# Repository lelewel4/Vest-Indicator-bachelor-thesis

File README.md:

The engineering diploma thesis describes the design of a signal vest for an electric scooter driver based on wireless communication and STM32 microcontrollers.

The work contains a short introduction to the subject of e-scooters, after which the goal and scope of the project were defined. Existing commercial signal vest solutions were also reviewed. Then, the components enabling wireless communication were analyzed and development kits were selected. The entire project was divided into two parts: transmitting and receiving. Their appropriate functionality and requirements are outlined. Both parts discuss and justify the choice of specific electronic components. Electrical diagrams and printed circuits designed in KiCad are also presented. After this part, the PCBs were manufactured along with the assembly of elements. The subsections devoted to the software present the CubeMX environment, block diagrams, used libraries and interesting fragments of the source code written in C. Then, in the Tinkercad program, the appropriate housings were designed and manufactured in 3D technology. After assembling the project, functional tests were carried out.
The summary contains conclusions and further development directions for the project of a signaling vest for an electric scooter driver.

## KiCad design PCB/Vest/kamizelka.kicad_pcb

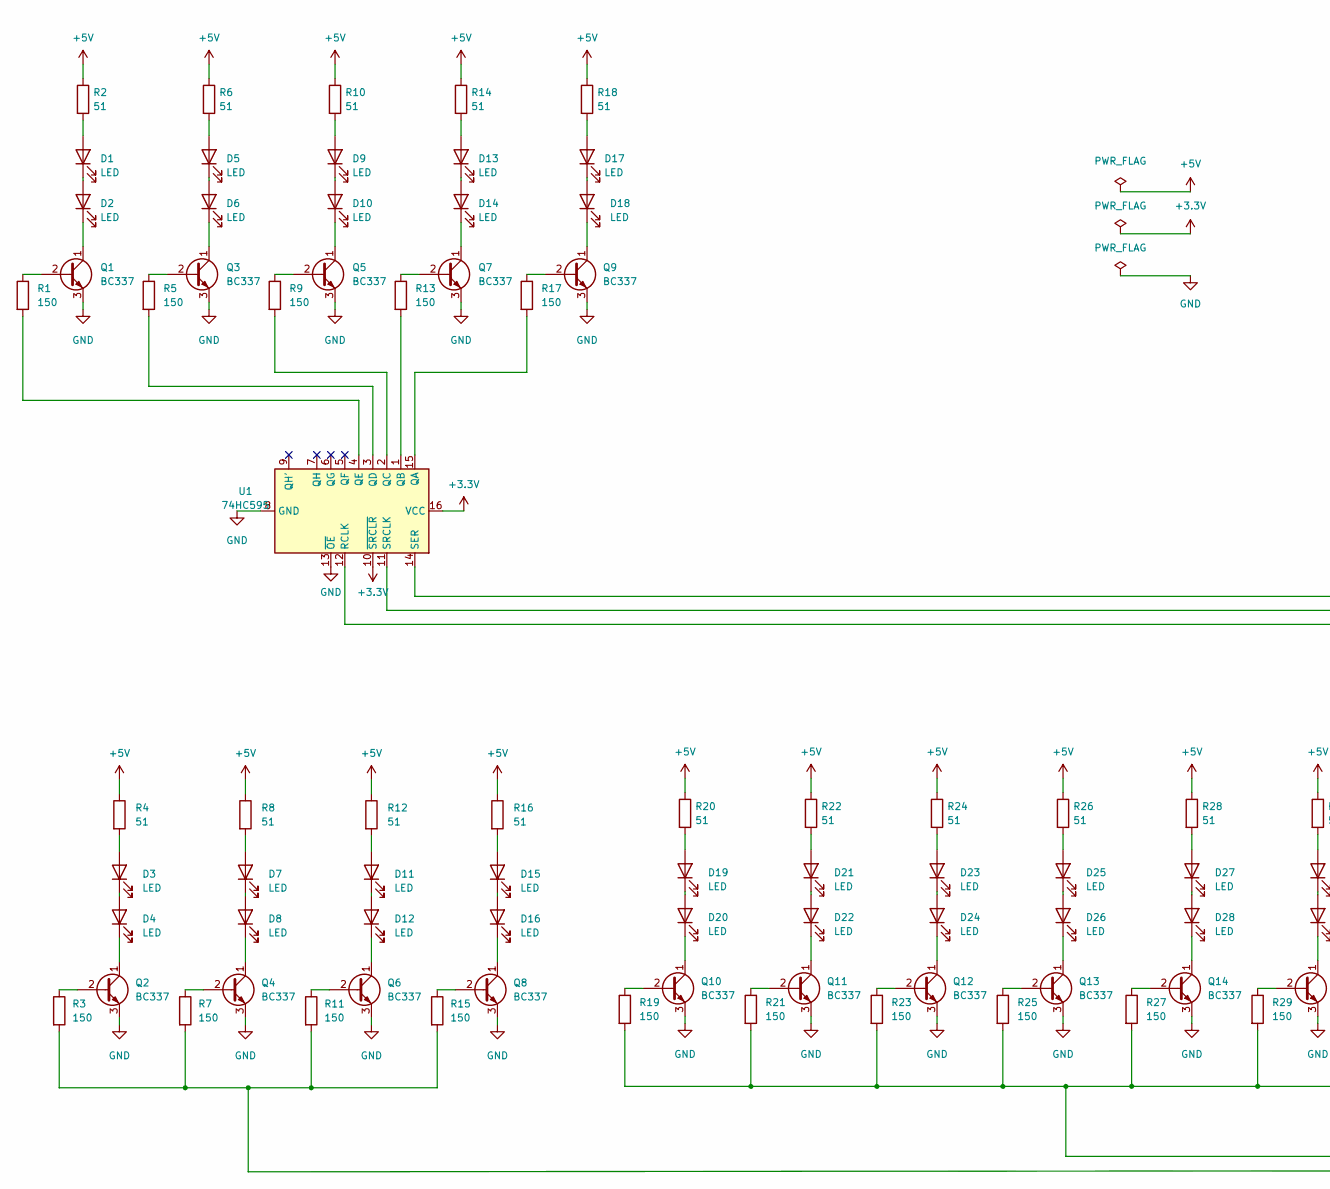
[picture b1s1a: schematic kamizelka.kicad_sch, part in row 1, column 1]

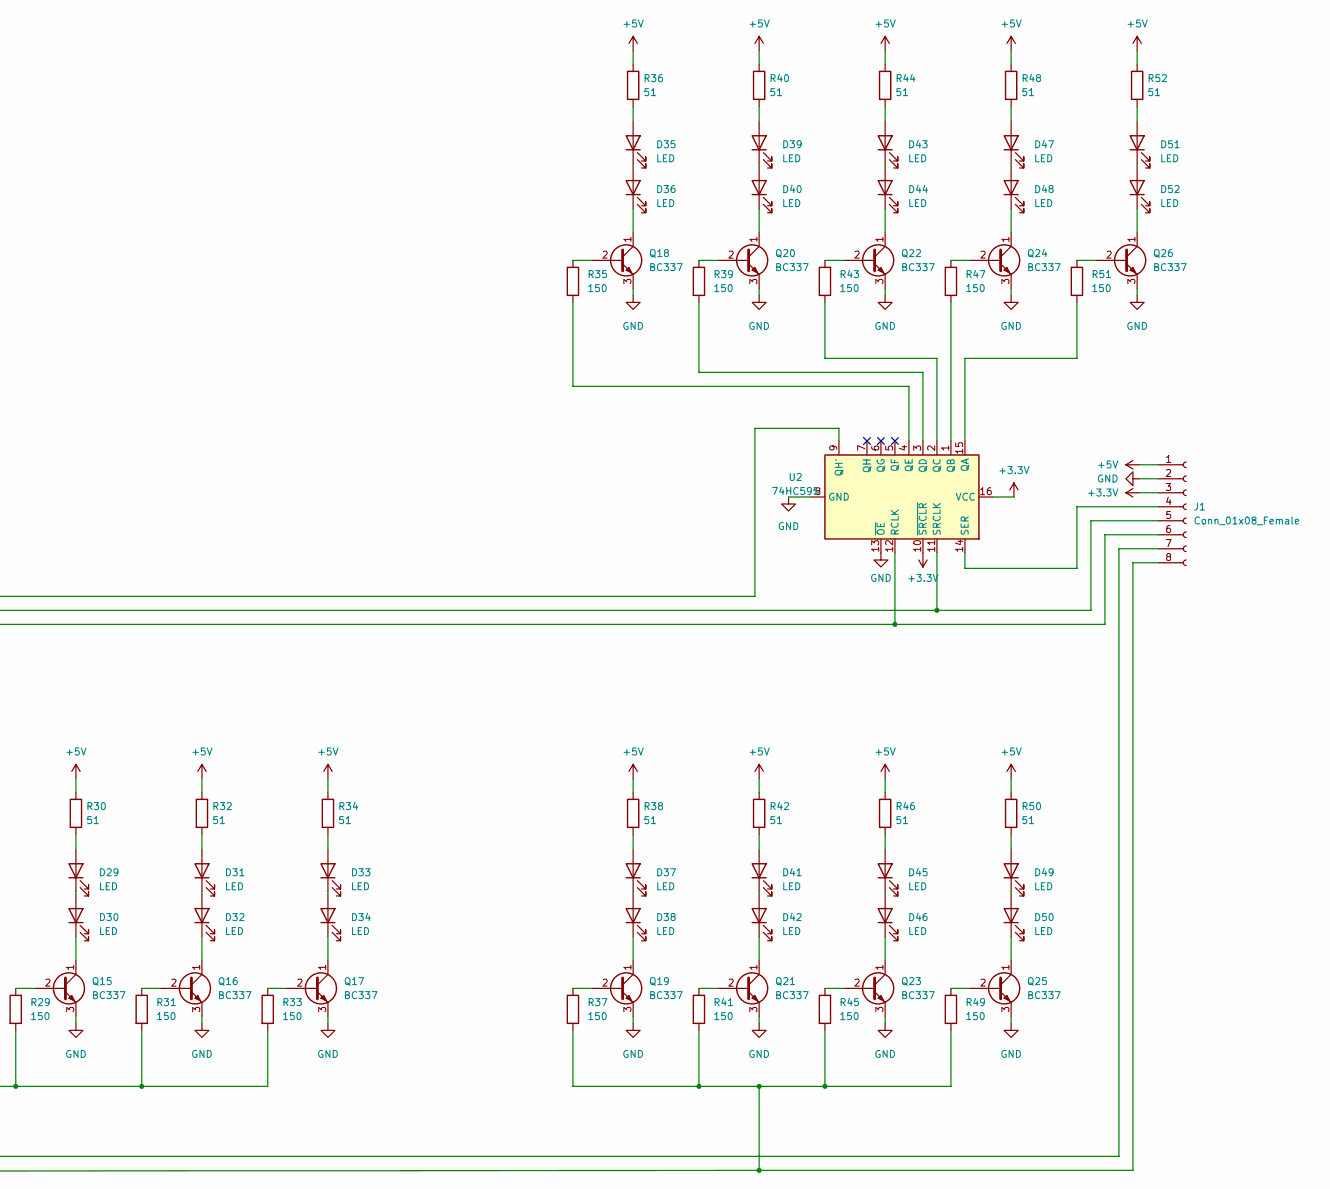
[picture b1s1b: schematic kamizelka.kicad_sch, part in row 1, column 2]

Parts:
D1, D2, D3, D4, D5, D6, D7, D8, D9, D10, D11, D12, D13, D14, D15, D16, D17, D18, D19, D20, D21, D22, D23, D24, D25, D26, D27, D28, D29, D30, D31, D32, D33, D34, D35, D36, D37, D38, D39, D40, D41, D42, D43, D44, D45, D46, D47, D48, D49, D50, D51, D52: LED; LED_D5.0mm
J1: Conn_01x08_Female; PinHeader_1x08_P2.54mm_Horizontal
Q1, Q2, Q3, Q4, Q5, Q6, Q7, Q8, Q9, Q10, Q11, Q12, Q13, Q14, Q15, Q16, Q17, Q18, Q19, Q20, Q21, Q22, Q23, Q24, Q25, Q26: BC337; TO-92_Inline
R1, R3, R5, R7, R9, R11, R13, R15, R17, R19, R21, R23, R25, R27, R29, R31, R33, R35, R37, R39, R41, R43, R45, R47, R49, R51: 150; R_Axial_DIN0207_L6.3mm_D2.5mm_P10.16mm_Horizontal
R2, R4, R6, R8, R10, R12, R14, R16, R18, R20, R22, R24, R26, R28, R30, R32, R34, R36, R38, R40, R42, R44, R46, R48, R50, R52: 51; R_Axial_DIN0207_L6.3mm_D2.5mm_P10.16mm_Horizontal
U1, U2: 74HC595; DIP-16_W7.62mm_LongPads

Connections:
+3V3: J1.3, U1.10 (~SRCLR), U1.16 (VCC), U2.10 (~SRCLR), U2.16 (VCC)
+5V: J1.1, R2.1, R4.1, R6.1, R8.1, R10.1, R12.1, R14.1, R16.1, R18.1, R20.1, R22.1, R24.1, R26.1, R28.1, R30.1, R32.1, R34.1, R36.1, R38.1, R40.1, R42.1, R44.1, R46.1, R48.1, R50.1, R52.1
GND: J1.2, Q1.3 (E), Q2.3 (E), Q3.3 (E), Q4.3 (E), Q5.3 (E), Q6.3 (E), Q7.3 (E), Q8.3 (E), Q9.3 (E), Q10.3 (E), Q11.3 (E), Q12.3 (E), Q13.3 (E), Q14.3 (E), Q15.3 (E), Q16.3 (E), Q17.3 (E), Q18.3 (E), Q19.3 (E), Q20.3 (E), Q21.3 (E), Q22.3 (E), Q23.3 (E), Q24.3 (E), Q25.3 (E), Q26.3 (E), U1.8 (GND), U1.13 (~OE), U2.8 (GND), U2.13 (~OE)
unnamed: D1.1 (K), D2.2 (A)
unnamed: D1.2 (A), R2.2
unnamed: D2.1 (K), Q1.1 (C)
unnamed: D3.1 (K), D4.2 (A)
unnamed: D3.2 (A), R4.2
unnamed: D4.1 (K), Q2.1 (C)
unnamed: D5.1 (K), D6.2 (A)
unnamed: D5.2 (A), R6.2
unnamed: D6.1 (K), Q3.1 (C)
unnamed: D7.1 (K), D8.2 (A)
unnamed: D7.2 (A), R8.2
unnamed: D8.1 (K), Q4.1 (C)
unnamed: D9.1 (K), D10.2 (A)
unnamed: D9.2 (A), R10.2
unnamed: D10.1 (K), Q5.1 (C)
unnamed: D11.2 (A), R12.2
unnamed: D12.1 (K), Q6.1 (C)
unnamed: D11.1 (K), D12.2 (A)
unnamed: D13.1 (K), D14.2 (A)
unnamed: D13.2 (A), R14.2
unnamed: D14.1 (K), Q7.1 (C)
unnamed: D15.1 (K), D16.2 (A)
unnamed: D15.2 (A), R16.2
unnamed: D16.1 (K), Q8.1 (C)
unnamed: D17.1 (K), D18.2 (A)
unnamed: D17.2 (A), R18.2
unnamed: D18.1 (K), Q9.1 (C)
unnamed: D19.1 (K), D20.2 (A)
unnamed: D19.2 (A), R20.2
unnamed: D20.1 (K), Q10.1 (C)
unnamed: D21.1 (K), D22.2 (A)
unnamed: D21.2 (A), R22.2
unnamed: D22.1 (K), Q11.1 (C)
unnamed: D23.1 (K), D24.2 (A)
unnamed: D23.2 (A), R24.2
unnamed: D24.1 (K), Q12.1 (C)
unnamed: D25.1 (K), D26.2 (A)
unnamed: D25.2 (A), R26.2
unnamed: D26.1 (K), Q13.1 (C)
unnamed: D27.1 (K), D28.2 (A)
unnamed: D27.2 (A), R28.2
unnamed: D28.1 (K), Q14.1 (C)
unnamed: D29.1 (K), D30.2 (A)
unnamed: D29.2 (A), R30.2
unnamed: D30.1 (K), Q15.1 (C)
unnamed: D31.1 (K), D32.2 (A)
unnamed: D31.2 (A), R32.2
unnamed: D32.1 (K), Q16.1 (C)
unnamed: D33.1 (K), D34.2 (A)
unnamed: D33.2 (A), R34.2
unnamed: D34.1 (K), Q17.1 (C)
unnamed: D35.1 (K), D36.2 (A)
unnamed: D35.2 (A), R36.2
unnamed: D36.1 (K), Q18.1 (C)
unnamed: D37.1 (K), D38.2 (A)
unnamed: D37.2 (A), R38.2
unnamed: D38.1 (K), Q19.1 (C)
unnamed: D39.1 (K), D40.2 (A)
unnamed: D39.2 (A), R40.2
unnamed: D40.1 (K), Q20.1 (C)
unnamed: D41.1 (K), D42.2 (A)
unnamed: D41.2 (A), R42.2
unnamed: D42.1 (K), Q21.1 (C)
unnamed: D43.1 (K), D44.2 (A)
unnamed: D43.2 (A), R44.2
unnamed: D44.1 (K), Q22.1 (C)
unnamed: D45.1 (K), D46.2 (A)
unnamed: D45.2 (A), R46.2
unnamed: D46.1 (K), Q23.1 (C)
unnamed: D47.1 (K), D48.2 (A)
unnamed: D47.2 (A), R48.2
unnamed: D48.1 (K), Q24.1 (C)
unnamed: D49.1 (K), D50.2 (A)
unnamed: D49.2 (A), R50.2
unnamed: D50.1 (K), Q25.1 (C)
unnamed: D51.1 (K), D52.2 (A)
unnamed: D51.2 (A), R52.2
unnamed: D52.1 (K), Q26.1 (C)
unnamed: J1.4, U2.14 (SER)
unnamed: J1.5, U1.11 (SRCLK), U2.11 (SRCLK)
unnamed: J1.6, U1.12 (RCLK), U2.12 (RCLK)
unnamed: J1.7, R19.2, R21.2, R23.2, R25.2, R27.2, R29.2, R31.2, R33.2
unnamed: J1.8, R3.2, R7.2, R11.2, R15.2, R37.2, R41.2, R45.2, R49.2
unnamed: Q1.2 (B), R1.1
unnamed: Q2.2 (B), R3.1
unnamed: Q3.2 (B), R5.1
unnamed: Q4.2 (B), R7.1
unnamed: Q5.2 (B), R9.1
unnamed: Q6.2 (B), R11.1
unnamed: Q7.2 (B), R13.1
unnamed: Q8.2 (B), R15.1
unnamed: Q9.2 (B), R17.1
unnamed: Q10.2 (B), R19.1
unnamed: Q11.2 (B), R21.1
unnamed: Q12.2 (B), R23.1
unnamed: Q13.2 (B), R25.1
unnamed: Q14.2 (B), R27.1
unnamed: Q15.2 (B), R29.1
unnamed: Q16.2 (B), R31.1
unnamed: Q17.2 (B), R33.1
unnamed: Q18.2 (B), R35.1
unnamed: Q19.2 (B), R37.1
unnamed: Q20.2 (B), R39.1
unnamed: Q21.2 (B), R41.1
unnamed: Q22.2 (B), R43.1
unnamed: Q23.2 (B), R45.1
unnamed: Q24.2 (B), R47.1
unnamed: Q25.2 (B), R49.1
unnamed: Q26.2 (B), R51.1
unnamed: R1.2, U1.4 (QE)
unnamed: R5.2, U1.3 (QD)
unnamed: R9.2, U1.2 (QC)
unnamed: R13.2, U1.1 (QB)
unnamed: R17.2, U1.15 (QA)
unnamed: R35.2, U2.4 (QE)
unnamed: R39.2, U2.3 (QD)
unnamed: R43.2, U2.2 (QC)
unnamed: R47.2, U2.1 (QB)
unnamed: R51.2, U2.15 (QA)
unnamed: U1.14 (SER), U2.9 (QH')

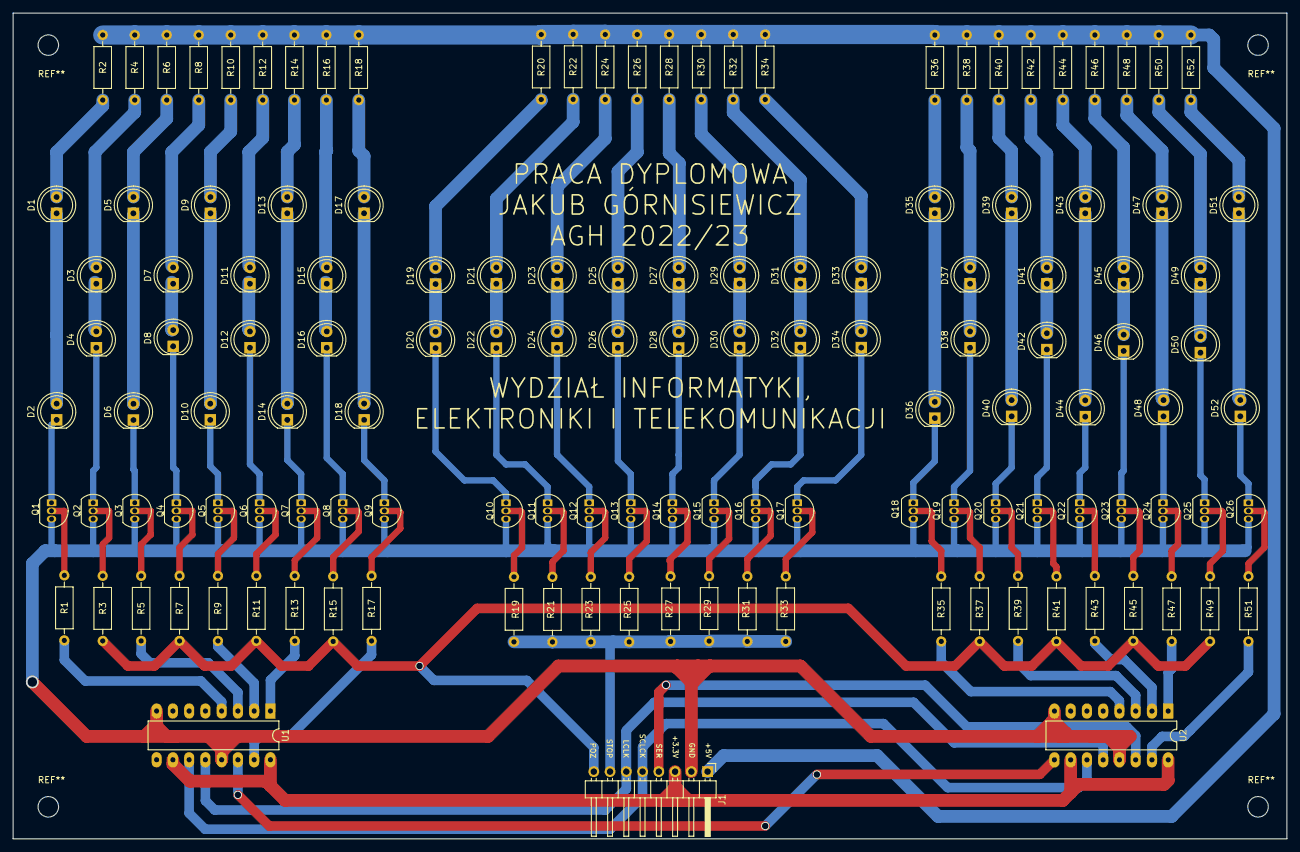
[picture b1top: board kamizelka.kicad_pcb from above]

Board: 2 copper layers, 199.0 x 129.0 mm, 133 parts (0 on the bottom side), 123 nets.

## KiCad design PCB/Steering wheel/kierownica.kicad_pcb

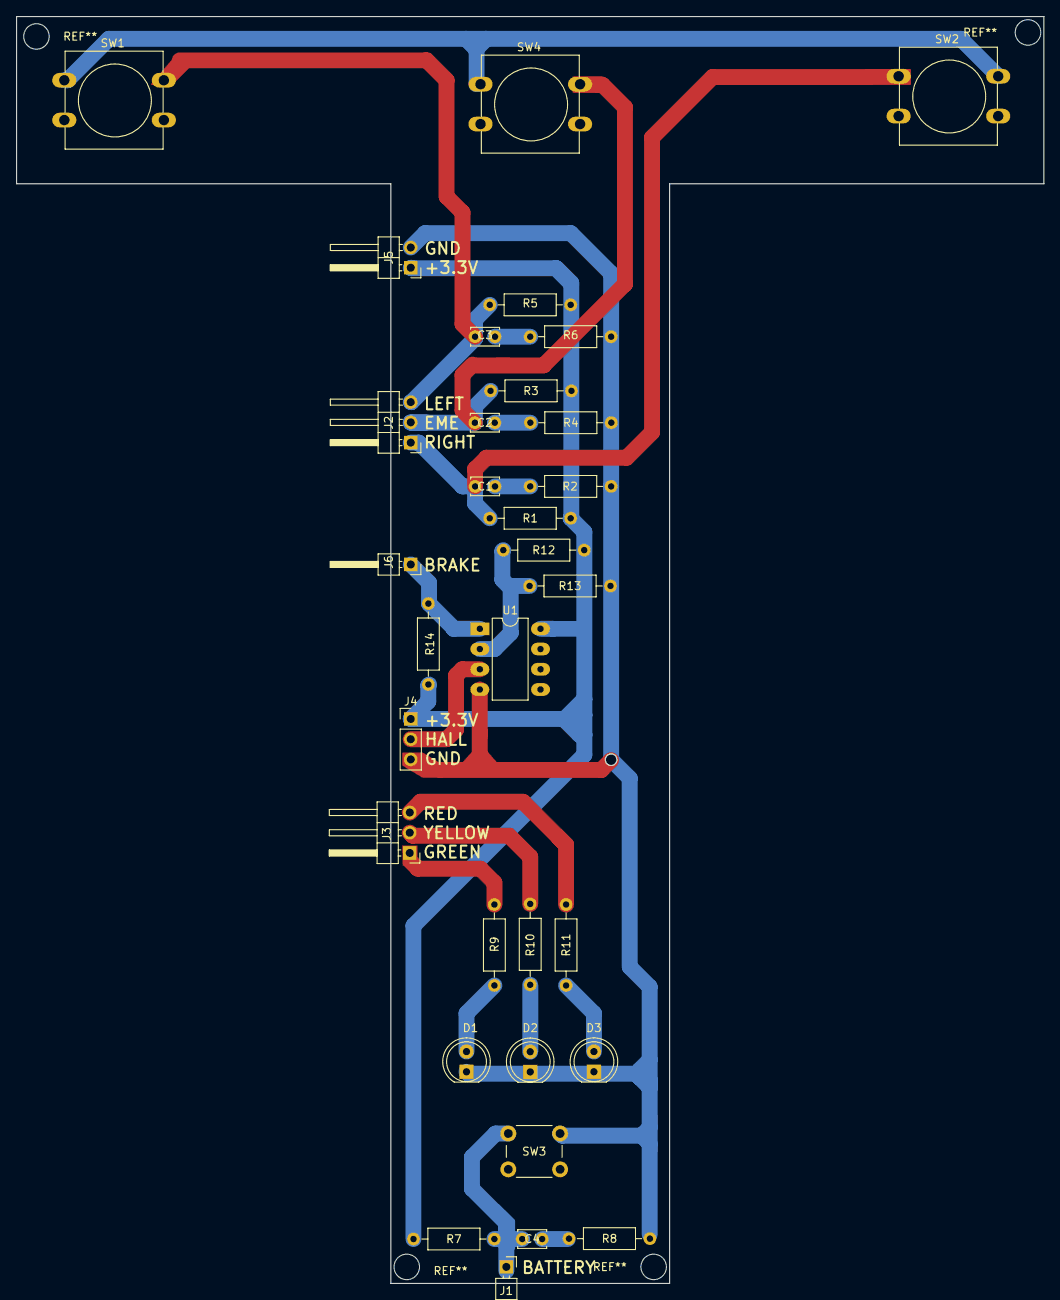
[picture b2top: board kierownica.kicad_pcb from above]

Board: 2 copper layers, 129.0 x 159.1 mm, 32 parts (0 on the bottom side), 19 nets.

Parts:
C1, C2, C3, C4: 100n; C_Disc_D3.4mm_W2.1mm_P2.50mm
D1: LED_RED; LED_D5.0mm
D2: LED_YELLOW; LED_D5.0mm
D3: LED_GREEN; LED_D5.0mm
J1, J6: Conn_01x01_Female; PinHeader_1x01_P2.54mm_Horizontal
J2, J3: Conn_01x03_Female; PinHeader_1x03_P2.54mm_Horizontal
J4: Conn_01x03_Female; PinHeader_1x03_P2.54mm_Vertical
J5: Conn_01x02_Female; PinHeader_1x02_P2.54mm_Horizontal
R1, R3, R5, R7: 4.7k; R_Axial_DIN0207_L6.3mm_D2.5mm_P10.16mm_Horizontal
R2, R4, R6, R8: 100; R_Axial_DIN0207_L6.3mm_D2.5mm_P10.16mm_Horizontal
R9, R10, R11: 76,4; R_Axial_DIN0207_L6.3mm_D2.5mm_P10.16mm_Horizontal
R12: 330; R_Axial_DIN0207_L6.3mm_D2.5mm_P10.16mm_Horizontal
R13: 130; R_Axial_DIN0207_L6.3mm_D2.5mm_P10.16mm_Horizontal
R14: 4,7k; R_Axial_DIN0207_L6.3mm_D2.5mm_P10.16mm_Horizontal
SW1: SW_LEFT; SW_PUSH-12mm
SW2: SW_RIGHT; SW_PUSH-12mm
SW3: SW_BATTERY; SW_PUSH_6mm_H7.3mm
SW4: SW_EMERGENCY; SW_PUSH-12mm
U1: LM393; DIP-8_W7.62mm_LongPads

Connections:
+3V3: J4.1, J5.1, R1.2, R3.2, R5.2, R7.2, R12.1, R14.1
GND: D1.1 (K), D2.1 (K), D3.1 (K), J4.3, J5.2, R2.2, R4.2, R6.2, R8.2, R13.2, SW1.1, SW2.1, SW3.1, SW4.1
unnamed: C1.1, J2.1, R1.1
unnamed: C1.2, R2.1
unnamed: C2.1, J2.2, R3.1
unnamed: C2.2, R4.1
unnamed: C3.1, J2.3, R5.1
unnamed: C3.2, R6.1
unnamed: C4.1, J1.1, R7.1
unnamed: C4.2, R8.1
unnamed: D1.2 (A), R9.2
unnamed: D2.2 (A), R10.2
unnamed: D3.2 (A), R11.2
unnamed: J3.1, R9.1
unnamed: J3.2, R10.1
unnamed: J3.3, R11.1
unnamed: J4.2, U1.3 (+)
unnamed: J6.1, R14.2, U1.1
unnamed: R12.2, R13.1, U1.2 (-)

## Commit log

2023-10-08 Added to GIT
